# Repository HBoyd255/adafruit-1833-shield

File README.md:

# Adafruit 1833 Shield

This is a KiCad library representing the
[Adafruit 1833 USB Micro B](https://www.adafruit.com/product/1833), as a shield.

This allows for a USB Micro B connector to be added to a PCB, without the need
for surface mount soldering.

## Images

Here is what the footprint looks like in KiCad:

### Footprint

### Silkscreen

### 3D Model

## Setup

To get the library working, you need to add path of this repository to the KiCad
library search path. This can be done by going to
`Preferences -> Configure Paths` and adding the path with the name
`Adafruit_1833_Shield`.

## License

This footprint is derived from the original board by Adafruit, used under CC
BY-SA 3.0. This library is also licensed under CC BY-SA 3.0.

The original board can be found at:
[github.com/adafruit/Adafruit-SMT-Breakout-PCBs](https://github.com/adafruit/Adafruit-SMT-Breakout-PCBs).

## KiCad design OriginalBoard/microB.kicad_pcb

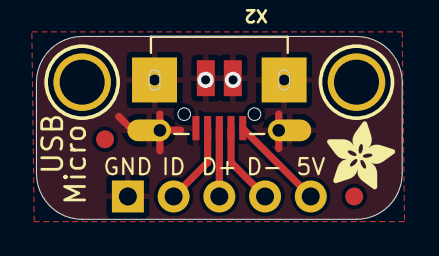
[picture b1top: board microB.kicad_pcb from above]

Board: 2 copper layers, 20.3 x 10.2 mm, 7 parts (0 on the bottom side), 5 nets.

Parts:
FID1, FID2: FIDUCIAL""; FIDUCIAL_1MM
JP2: 1X05_ROUND_70
U$1, U$2: MOUNTINGHOLE2.5; MOUNTINGHOLE_2.5_PLATED
U$4: ADAFRUIT_3.5MM
X2: 4UCONN_20329

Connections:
D+: JP2.3, X2.D+
D-: JP2.4, X2.D-
GND: JP2.1, X2.BASE@1, X2.BASE@2, X2.GND, X2.SPRT@1, X2.SPRT@2, X2.SPRT@3, X2.SPRT@4
ID: JP2.2, X2.ID
VBUS: JP2.5, X2.VBUS

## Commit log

2024-07-23 Created repo
2024-07-23 Added license
2024-07-23 Shortened name
2024-07-23 Imported existing board
2024-07-23 Grouped edge cuts
2024-07-23 Created footprint
2024-07-23 Added header pins to footprint
2024-07-23 Added 3d model of shield
2024-07-23 Moved silkscreen
2024-07-23 Added images
2024-07-23 Replaces pads for edge cut holes
2024-07-23 Added connector to silkscreen
2024-07-28 Updated font
2024-07-28 Moved text
